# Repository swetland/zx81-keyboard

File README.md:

### ZX81 Mechanical Keyboard

A mechanical keyboard that's compatible with the Sinclair ZX81, as well as the
ZX81+38 modern recreation of that machine.  This repository contains all the
design files as well as various exported versions and images.  Please carefully
review any files before you use them to order hardware!

The KiCAD files for the schematic and layout are provided.
The [export](export/) directory contains PDF versions for convenient online
viewing.  The [gerbers](gerbers/) directory contains the exported gerbers
I generated for an order of five PCBs from JLCPCB.

The custom keycaps were ordered via wasdkeyboards:
https://www.wasdkeyboards.com/61-key-custom-cherry-mx-keycap-set.html

In the [keycaps](keycaps/) directory there are two versions of the SVG files,
based on the template provided by wasd.  The "paths" version has been converted
to paths and is suitable for submitting for an order.  The other version keeps
the text elements as text for easier editing, but must be converted to paths
before using for ordering.

### Need a ZX81 to add a keyboard to?

The ZX81+38 project is a modern recreation of the ZX81 mainboard using
74xx series ICs, similar to the ZX80, instead of the (no longer manufactured)
ULA used in vintage ZX81s.  Check it out:

https://github.com/mahjongg2/ZX81plus38

https://revspace.nl/ZX81plus38_simple_to_build_ZX-81_clone 

https://forums.raspberrypi.com/viewtopic.php?t=254492

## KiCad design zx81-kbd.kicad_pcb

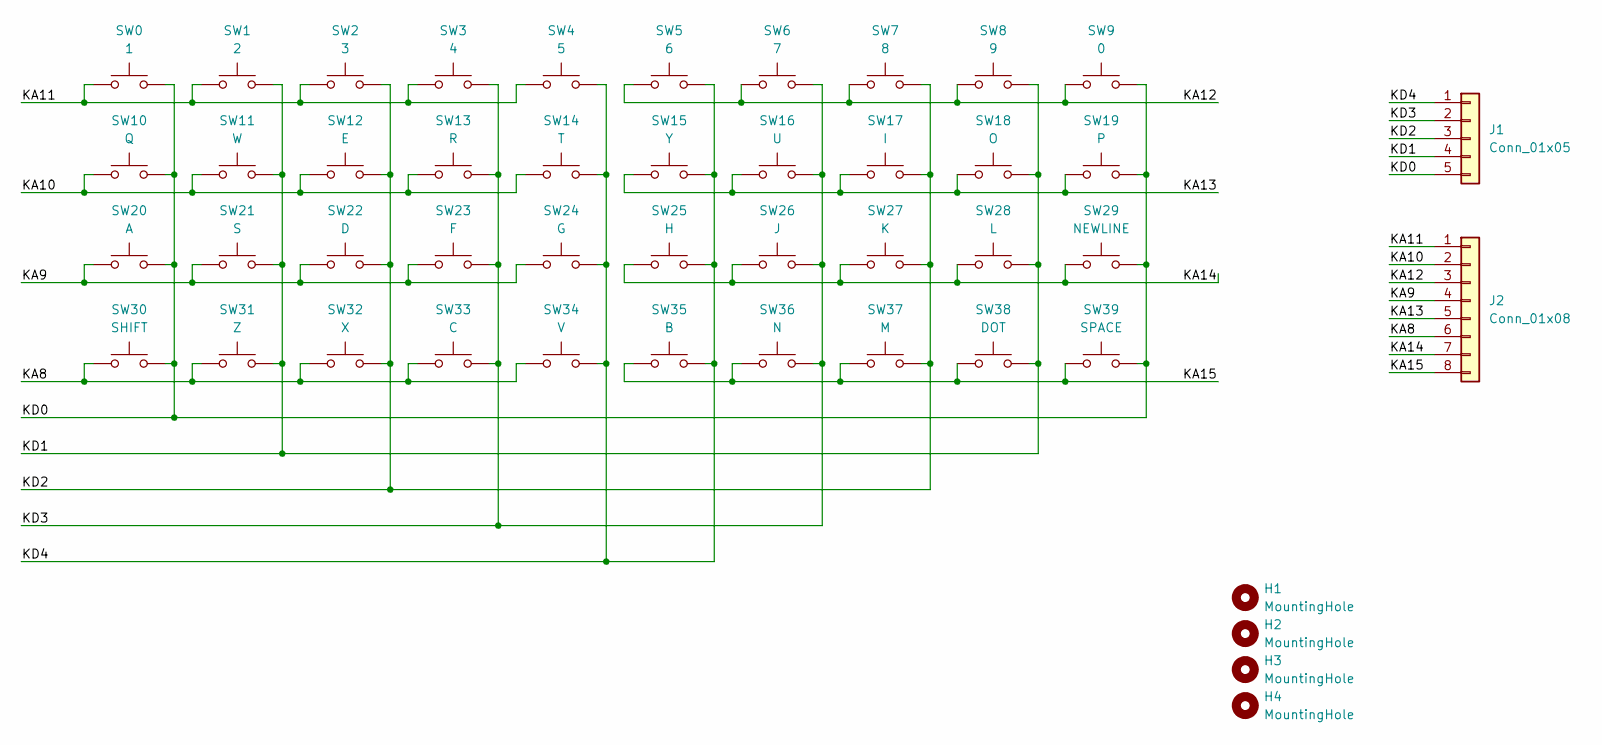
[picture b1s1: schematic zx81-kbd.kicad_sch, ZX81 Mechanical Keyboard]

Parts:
H1, H2, H3, H4: MountingHole; MountingHole_3.2mm_M3
J1: Conn_01x05; PinHeader_1x05_P2.54mm_Vertical
J2: Conn_01x08; PinHeader_1x08_P2.54mm_Vertical
SW0: 1; SW_Cherry_MX_1.00u_PCB
SW1: 2; SW_Cherry_MX_1.00u_PCB
SW2: 3; SW_Cherry_MX_1.00u_PCB
SW3: 4; SW_Cherry_MX_1.00u_PCB
SW4: 5; SW_Cherry_MX_1.00u_PCB
SW5: 6; SW_Cherry_MX_1.00u_PCB
SW6: 7; SW_Cherry_MX_1.00u_PCB
SW7: 8; SW_Cherry_MX_1.00u_PCB
SW8: 9; SW_Cherry_MX_1.00u_PCB
SW9: 0; SW_Cherry_MX_1.00u_PCB
SW10: Q; SW_Cherry_MX_1.00u_PCB
SW11: W; SW_Cherry_MX_1.00u_PCB
SW12: E; SW_Cherry_MX_1.00u_PCB
SW13: R; SW_Cherry_MX_1.00u_PCB
SW14: T; SW_Cherry_MX_1.00u_PCB
SW15: Y; SW_Cherry_MX_1.00u_PCB
SW16: U; SW_Cherry_MX_1.00u_PCB
SW17: I; SW_Cherry_MX_1.00u_PCB
SW18: O; SW_Cherry_MX_1.00u_PCB
SW19: P; SW_Cherry_MX_1.00u_PCB
SW20: A; SW_Cherry_MX_1.00u_PCB
SW21: S; SW_Cherry_MX_1.00u_PCB
SW22: D; SW_Cherry_MX_1.00u_PCB
SW23: F; SW_Cherry_MX_1.00u_PCB
SW24: G; SW_Cherry_MX_1.00u_PCB
SW25: H; SW_Cherry_MX_1.00u_PCB
SW26: J; SW_Cherry_MX_1.00u_PCB
SW27: K; SW_Cherry_MX_1.00u_PCB
SW28: L; SW_Cherry_MX_1.00u_PCB
SW29: NEWLINE; SW_Cherry_MX_1.00u_PCB
SW30: SHIFT; SW_Cherry_MX_1.00u_PCB
SW31: Z; SW_Cherry_MX_1.00u_PCB
SW32: X; SW_Cherry_MX_1.00u_PCB
SW33: C; SW_Cherry_MX_1.00u_PCB
SW34: V; SW_Cherry_MX_1.00u_PCB
SW35: B; SW_Cherry_MX_1.00u_PCB
SW36: N; SW_Cherry_MX_1.00u_PCB
SW37: M; SW_Cherry_MX_1.00u_PCB
SW38: DOT; SW_Cherry_MX_1.00u_PCB
SW39: SPACE; SW_Cherry_MX_1.00u_PCB

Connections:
/KA8: J2.6, SW30.1, SW31.1, SW32.1, SW33.1, SW34.1
/KA9: J2.4, SW20.1, SW21.1, SW22.1, SW23.1, SW24.1
/KA10: J2.2, SW10.1, SW11.1, SW12.1, SW13.1, SW14.1
/KA11: J2.1, SW0.1, SW1.1, SW2.1, SW3.1, SW4.1
/KA12: J2.3, SW5.1, SW6.1, SW7.1, SW8.1, SW9.1
/KA13: J2.5, SW15.1, SW16.1, SW17.1, SW18.1, SW19.1
/KA14: J2.7, SW25.1, SW26.1, SW27.1, SW28.1, SW29.1
/KA15: J2.8, SW35.1, SW36.1, SW37.1, SW38.1, SW39.1
/KD0: J1.5, SW0.2, SW9.2, SW10.2, SW19.2, SW20.2, SW29.2, SW30.2, SW39.2
/KD1: J1.4, SW1.2, SW8.2, SW11.2, SW18.2, SW21.2, SW28.2, SW31.2, SW38.2
/KD2: J1.3, SW2.2, SW7.2, SW12.2, SW17.2, SW22.2, SW27.2, SW32.2, SW37.2
/KD3: J1.2, SW3.2, SW6.2, SW13.2, SW16.2, SW23.2, SW26.2, SW33.2, SW36.2
/KD4: J1.1, SW4.2, SW5.2, SW14.2, SW15.2, SW24.2, SW25.2, SW34.2, SW35.2

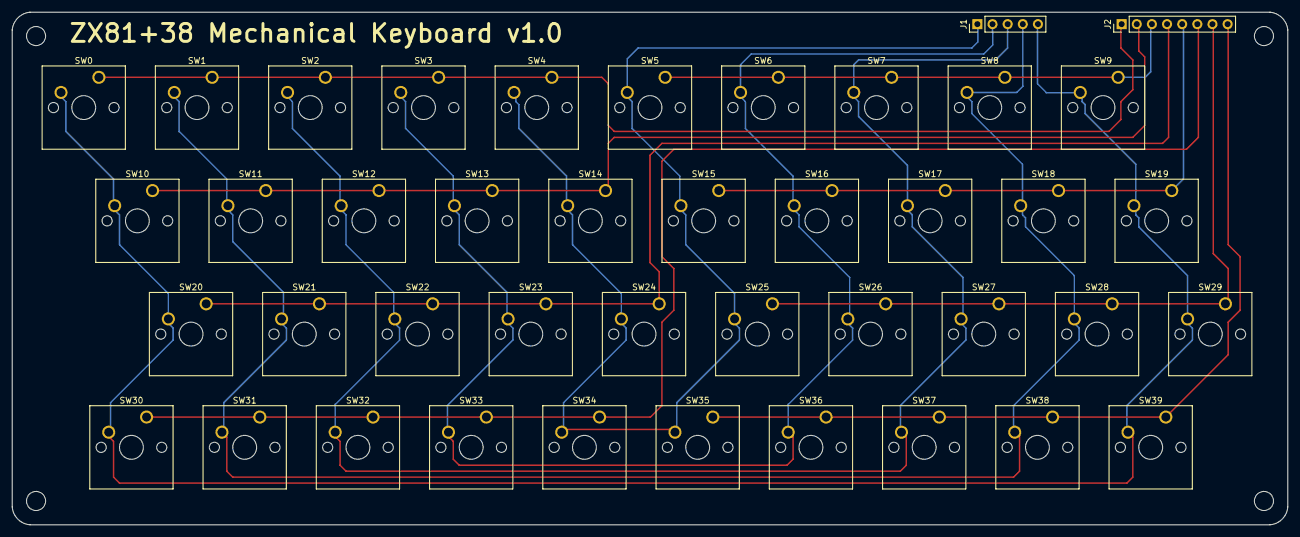
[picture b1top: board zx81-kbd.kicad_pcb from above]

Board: 2 copper layers, 214.0 x 86.0 mm, 46 parts (0 on the bottom side), 13 nets.

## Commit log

2023-06-13 Initial checkin of kicad files and LICENSE.
2023-06-13 Gerbers as sent to JLC PCB for fab.
2023-06-13 schematic and layout exported in PDF and PNG formats
2023-06-13 some pictures
2023-06-13 readme
2023-06-13 keycap designs
2023-06-13 fix typo
2023-06-13 fix a typo
2023-06-13 add ZX81+38 links

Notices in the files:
zx81-kbd.kicad_pcb:
Provided under the MIT License (0 clause)
Copyright 2022, Brian Swetland
